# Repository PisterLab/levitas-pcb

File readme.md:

# LeviTAS PCB

This is a PCB test platform originally built for the LeviTAS project.

A Raspberry Pi Pico microcontroller controls four 0-240V high voltage outputs and can simultaneously read from four FDC2112 capacitance sensors. The architecture and code should be straightforward to re-engineered to add more channels.

# Programming / Firmware

This is how to program the microcontroller.

## Introduction

This project uses the Raspberry Pi RP2350 microcontroller, which is mounted to a Raspberry Pi Pico 2 dev board that we solder onto the main project PCB. The dev board is cheap and convenient because in addition to the RP2350 itself it includes flash memory, an oscillator, and power circuitry that we'd otherwise have to include anyway. The programming is the same either way.

The RP2350 is uniquely good for our use case because we need (a) four I2C buses running in parallel to read FDC2112 capacitance sensors, for which we use the PIO modules available only on the RP2040 and RP2350, and (b) we'd like floating-point math support built into the hardware, which the RP2350 has but the RP2040 does not. An FPGA might accomplish roughly the same tasks but is much more expensive and complicated to use.

Programming the RP2350 microcontroller is officially supported in C++ or MicroPython. We use C++ to more easily write programs that satisfy tight timing constraints (e.g., making a control loop as fast as possible). See the Documentation section below for links to the official documentation.

Note we're specifically using the 2.0.0 version of the SDK (because that's what we started with and haven't bothered to update it). Updating this requires updating the pico-sdk subfolder, every mention of the SDK version in other configuration files, and the version of the picotool utility used to upload the software. To minimize compilation issues, we also specifically chose to put the SDK files inside this git repo instead of requiring them to be downloaded to an external directory and linked.

## Installation and Running

Use the following steps to set up a software build environment for the Pico firmware on Linux or Windows, or follow the [official getting started guide](https://datasheets.raspberrypi.com/pico/getting-started-with-pico.pdf) for more generic instructions.

On Linux:
- Install gcc-arm-none-eabi compiler (arm-non-eabi-gcc on nixos)
- Install newlib
- Install cmake and gnumake
- Install picotool
- Install picotool udev rules
- In `firmware` folder, run `make build` to compile code and `make reload` to download and run (or `make` to do both).
- Use your favorite serial monitor to see data the Pico sends over USB.

On Windows:
- Install [Microsoft VS Code](https://code.visualstudio.com/) (This is preferable to VSCodium because the easiest way to read data from the Pico over USB is the Microsoft VS Code Serial Monitor extension, which doesn't work with VSCodium)
- Install the official [Raspberry Pi Pico Visual Studio Code extension](https://marketplace.visualstudio.com/items?itemName=raspberry-pi.raspberry-pi-pico)
- Open the `firmware` folder in VS Code. The Pi Pico extension should automatically detect this as a Pico project, and enable several commands under its quick access menu (click the extension icon on the Activity Bar, then under "Project" should be "Debug Project", "Compile Project", "Run Project (USB)", etc).
- Use the following commands:
  - "Compile Project" will compile (only) the software and put the compiled executables in a `build` subfolder, but note that "Configure CMake" must be run first.
  - "Configure CMake" will create a `build` subfolder and prepare the compilation based on configuration information in the `CMakeLists.txt` file. This is run automatically when the folder is opened in VS Code if recognized by the Pico extension. NOTE: THIS MUST BE MANUALLY RE-RUN EVERY TIME YOU CHANGE `CMakeLists.txt` FOR THE CHANGES TO BE APPLIED!
  - "Run Project (USB)" will load the program onto a Rasberry Pi Pico 2 board connected over USB (specifically, by running the `picotool` command line utility). If the Pico is in BOOTSEL mode (achieved by holding down the BOOTSEL button before plugging in USB) it will probably work immediately. If not, uploading can still work if USB communication was enabled on the already-running Pico program (which it is for this software, as per `CMakeLists.txt`), though you might need to press "Run Project (USB)" twice.
  - "Debug Project" and "Flash Project (SWD)" do not work without use of the Raspberry Pi Debug Probe (which we don't have).
- To see data the Pico is sending over USB, open the "SERIAL MONITOR" tab on the lower VS Code panel that also has "TERMINAL", "DEBUG CONSOLE", etc., set to 115200 baud and the correct COM port. Note this requires `pico_enable_stdio_usb(levitas 1)` to be set in `CMakeLists.txt` and `stdio_init_all();` to be called in `main.c` (which they are).

## Notable Firmware files

Inside the `firmware` folder:

- `CMakeLists.txt` configures compilation, and must be manually changed to include new source code files or other settings (e.g., importing a new sublibrary for the Pico SDK)
- `src/main.c` is the main source code file and holds the main LeviTAS control loop.
  - by default, this only prints capacitive sensor readings over USB; high voltage is set to zero
  - uncomment code in the main loop to enable high voltage output
- `src/pio_i2c.c`, `src/pio_i2c.h`, and `src/pio_i2c.pio` together form a library that can run I2C communication via the Pico PIOs. `src/main.c` uses this library to run four I2C ports in parallel (to connect to four FDC2112 chips).
- the following test code is unused but can be enabled by changing `CMakeLists.txt` to make them the main project file instead of `main.c`:
  - `src/test_fdc2112_i2c.c` tests only two of the four connected FDC2112 chips by using the two hardware built-in I2C modules (instead of PIO)
  - `src/test_fdc2112_pio_i2c.c` tests all four connected FDC2112 chips using the PIO library, and is almost identical to code in `src/main.c`.
  - `src/test_max5715_spi.c` tests the MAX5715 DAC and high voltage output, and is almost identical to code in `src/main.c`.
  - `src/test_mpu6050_i2c.c` displays data the MPU6050 accelerometer on the PCB motherboard using one of the hardware built-in I2C modules.

Other files:
- `Makefile` is used only for compiling on Linux, not for VS Code
- `.vscode` and `pico_sdk_import.cmake` are used only for VS Code with the official Pico VS Code extension, not on Linux
- the `build` subfolder is automatically generated by cmake when compiling and contains compiled executables in several formats, including UF2.

## Data Collection

The `data-collection/collect-data.py` and `data-collection/graph-data.py` Python programs in the `data-collection` subfolder of the main git repo can be used to automatically read the data the microcontroller sends over USB, then graph it. This provides much more useful data than manually looking at the printed output in a serial monitor.

## Some Useful Notes

There are several ways to upload code to a RP2040 or RP2350 chip:
1. Put into BOOTSEL mode (on Pi Pico dev board, hold down BOOTSEL buton when connecting power/USB), at which point the built-in ROM makes it act like a USB mass storage device. Upload file. (To verify file uploaded correctly, use picotool)
2. Put into BOOTSEL mode, use picotool to upload file
3. If USB communication enabled, can use picotool to force exit into BOOTSEL mode (use "picotool load -f" or "-F") then reboot (convenient!). There's no need to press the BOOTSEL button anymore. Note that sometimes this doesn't work on the first try, but repeating the process usually works.
4. Use SWD debugging interface.
Using the BOOTSEL mode (options 1,2) is necessary on a new chip, but afterward, as long as a program with USB communication enabled is running, option 3 is much more convenient. This is what we generally use.

Notes on the C/C++ SDK (from PDF manual):
- Consists of a large number of CMake libraries (in pico-sdk/src/rp2_common), which must be linked in the per-project CMakeLists.txt
  - The default library used in most examples is pico_stdlib, which includes several other libraries
  - the include files are typically in pico-sdk/src/rp2_common/(CMake library name)/include/(pico, hardware, gpio, etc)/(header.h)
- Apparently has some ability to build/debug running on the host operating system instead of the RP2040?
- Definitions for dev boards are in pico-sdk/src-boards/include/boards/
- The PDF manual has a bunch of examples
- Standard stdin/stdout can use (chapter 2.7):
  - UART (easy) (enabled by default) (disable by calling pico_enable_stdio_uart in CMakeLists.txt)
  - a USB CDC ACM virtual serial port (via TinyUSB) (enable by linking pico_stdio_usb or calling pico_enable_stdio_usb in CMakeLists.txt)
        (this is generally my preference?)
  - serial wire debug link (semihosting)
  - Segger RTT
- Can use bi_decl() in C code to store information in compiled binaries that picotool can access (e.g., comments, pin numbers)

## Documentation

There is a large amount of good official documentation at the following links. The most useful documentation is noted.

https://www.raspberrypi.com/documentation/microcontrollers/

RP2350 microcontroller:
- https://www.raspberrypi.com/products/rp2350/
- (good details on RP2350 hardware/capabilities) https://datasheets.raspberrypi.com/rp2350/rp2350-datasheet.pdf
- https://datasheets.raspberrypi.com/rp2350/hardware-design-with-rp2350.pdf
- https://datasheets.raspberrypi.com/rp2350/rp2350-product-brief.pdf

Pico and Pico 2 dev boards (which are almost identical):
- https://datasheets.raspberrypi.com/pico/pico-datasheet.pdf
- (good software getting-started guide) https://datasheets.raspberrypi.com/pico/getting-started-with-pico.pdf

Programming with C/C++:
- https://github.com/raspberrypi/pico-sdk
- (code examples) https://github.com/raspberrypi/pico-examples
- https://www.raspberrypi.com/documentation/microcontrollers/c_sdk.html
- https://www.raspberrypi.com/documentation/pico-sdk/index_doxygen.html
- (good software getting-started guide) https://datasheets.raspberrypi.com/pico/getting-started-with-pico.pdf
- (very thorough reference) https://datasheets.raspberrypi.com/pico/raspberry-pi-pico-c-sdk.pdf

Picotool:
- An official (and open source) CLI tool to work with compiled binaries and communicate with boards when in BOOTSEL mode (using the PICOBOOT interface; see RP2040 datasheet). Used to load and verify programs.
- https://github.com/raspberrypi/picotool

Raspberry Pi Debug Probe:
- Device to use UART or SWD debugging. Optional. We don't have one.
- https://www.raspberrypi.com/products/debug-probe/
- https://www.raspberrypi.com/documentation/microcontrollers/debug-probe.html

# More pictures

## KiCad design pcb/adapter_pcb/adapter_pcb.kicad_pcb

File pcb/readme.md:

# Bill of Materials

MOTHERBOARD

|--------------------+-----------+-----------------------------------------+----------+--------------------------|
| TOTAL QTY TO ORDER | PER BOARD | part                                    | COST PER | DigiKey part             |
|--------------------+-----------+-----------------------------------------+----------+--------------------------|
|                  5 |         1 | RP2350 Pico 2 board (SC1631)            | $5       | 2648-SC1631CT-ND         |
|--------------------+-----------+-----------------------------------------+----------+--------------------------|
|                    |         2 | 220ohm R thru-hole                      |          | S220QCT-ND               |
|                    |         1 | LED 5mm thru-hole white                 |          | BL-BZX3V4V-1-B02-ND      |
|                    |         1 | LED 5mm thru-hole red                   |          | 754-WP7113SURCK-ND       |
|--------------------+-----------+-----------------------------------------+----------+--------------------------|
|                    |         4 | 100nF 0603 SMD caps                     |          | 311-1523-1-ND            |
|                    |         3 | 4.7uF 0805 SMD caps                     |          | 1276-1244-1-ND           |
|--------------------+-----------+-----------------------------------------+----------+--------------------------|
|                  5 |         1 | MAX5715AAUD+T DAC                       | $14.6    | 175-MAX5715AAUD+TCT-ND   |
|--------------------+-----------+-----------------------------------------+----------+--------------------------|
|                  5 |         1 | HV264 opamp                             | $7.8     | 150-HV264TS-GCT-ND       |
|                    |         1 | 1N4004 diode thru-hole                  |          | 4878-1N4004CT-ND         |
|--------------------+-----------+-----------------------------------------+----------+--------------------------|
|                    |         4 | 5kohm, thru-hole, 400V                  |          | CF12JT4K70CT-ND          |
|                 12 |         4 | PTC fuse PTCCL05H100SBE                 | $0.99    | BC3368-ND                |
|--------------------+-----------+-----------------------------------------+----------+--------------------------|
|                  0 |         1 | Q025-5C power supply                    |          | -                        |
|                  5 |         1 | TVS diode P6KE6.8A-E3/54                | $0.32    | P6KE6.8A-E3/54GICT-ND    |
|                 10 |         1 | 1Mohm, thru-hole, 400V                  | $0.03    | RNV14FAL1M00             |
|                    |         1 | 10nF, thru-hole, 400V                   |          | 495-75587-1-ND           |
|--------------------+-----------+-----------------------------------------+----------+--------------------------|
|                  3 |         1 | Stemma MPU-6050 accelerometer breakout  | $12.95   | 1528-3886-ND             |
|--------------------+-----------+-----------------------------------------+----------+--------------------------|
|                  6 |         2 | ZIF socket                              | $24.49   | A305-ND                  |
|                    |        10 | jumpers                                 |          |                          |
|                    |         3 | 20x breakaway male header pins          |          | 2057-PH1-20-UA-ND        |
|                    |         3 | 20x female header pins                  |          | S7053-ND                 |
|--------------------+-----------+-----------------------------------------+----------+--------------------------|
|                    |         1 | solder paste?                           |          | 315-NC191AX35T5-ND       |
|                    |         1 | rubber feet?                            |          | 3M156065-ND              |
|--------------------+-----------+-----------------------------------------+----------+--------------------------|
|                    |         8 | 100nF 0603 SMD caps                     |          | 311-1523-1-ND            |
|                    |         8 | 4.7uF 0805 SMD caps                     |          | 1276-1244-1-ND           |
|--------------------+-----------+-----------------------------------------+----------+--------------------------|
|                 15 |         4 | cap sensor FDC2112QDNTRQ1               | $6.59    | 296-44560-1-ND           |
|                    |         8 | resistor SMD 4.7k 0603                  |          | 311-4.7KGRCT-ND          |
|                    |         8 | resistor SMD 470  0603                  |          | A129684CT-ND             |
|                    |         8 | resistor SMD 0  0603 (just in case)     |          | RMCF0603ZT0R00CT-ND      |
|                    |         4 | inductor SMD 18uH 0603 MLF1608C180KTA00 |          | 445-1028-1-ND            |
|                    |         4 | cap SMD 33pF 0603                       |          | 478-KGM15ACG1H330JTCT-ND |
|--------------------+-----------+-----------------------------------------+----------+--------------------------|

Generate PCB gerbers according to
https://www.pcbway.com/blog/help_center/Generate_Gerber_file_from_Kicad.html
- use copper, paste, silkscreen, mask, edge.cuts
- uncheck "use extended x2 format"
- drill file with "minimal header" and "suppress leading zeros"

When ordering:
- remove label option
- extra urgent

# Accelerometer

Attached for board leveling and reference data.

Using breakout board instead of individual chip because I don't trust my soldering for something that small.

Can use either Adafruit Stemma MPU-6050 breakout or Stemma ADXL345 breakout (same board size, slightly more expensive).

# Motherboard/daughterboard connection

We attach the sensor daughterboard with an IC ZIF socket (well, two sockets). We use this instead of standard 0.1" header pins and sockets because inserting or removing header pins takes significant force, which can significantly shake or warp the daughterboard and might break the fragile MEMS devices on top. Ultimately, of course, we want to build a levitation system capable of sustaining high external forces, but our initial prototypes may not immediately reach that goal. That said, the motherboard PCB has footprints such that it can be assembled with standard female header pins instead of ZIF sockets with no other change in functionality.

The specific ZIF sockets se use are 32-6554-11 "CONN IC DIP SOCKET ZIF 32POS GLD" or 32-6554-10 "CONN IC DIP SOCKET ZIF 32POS TIN" from Aries Electronics due to their relatively high availability and robust construction.

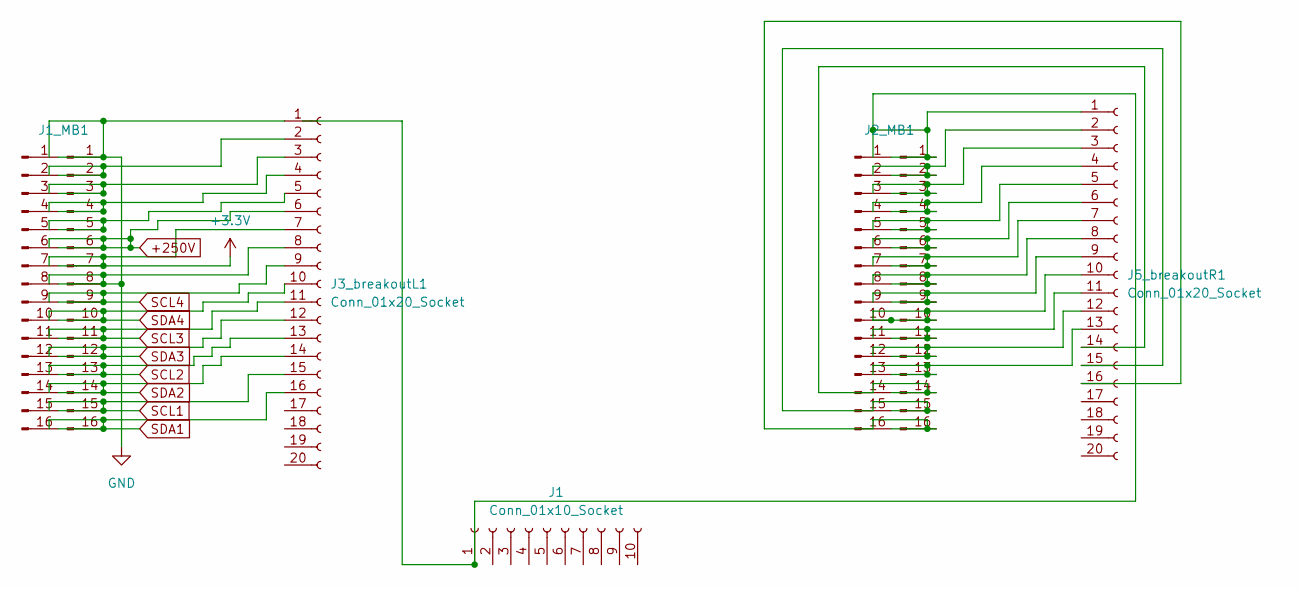
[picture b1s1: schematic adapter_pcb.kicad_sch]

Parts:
J1: Conn_01x10_Socket; wirebondarray-dteal
J1_MB1, J2_MB1, J3, J5: Conn_01x16_Pin; PinHeader_1x16_P2.54mm_Vertical
J3_breakoutL1, J5_breakoutR1: Conn_01x20_Socket; wirebondarray-1x20-emtan

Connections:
+3.3V: J1_MB1.7, J3.7, J3_breakoutL1.7
+250V: J1_MB1.6, J3.6, J3_breakoutL1.6
unnamed: J1_MB1.2, J3.2, J3_breakoutL1.2
unnamed: J1_MB1.3, J3.3, J3_breakoutL1.3
unnamed: J1_MB1.4, J3.4, J3_breakoutL1.4
unnamed: J1_MB1.5, J3.5, J3_breakoutL1.5
unnamed: J2_MB1.2, J5.2, J5_breakoutR1.2
unnamed: J2_MB1.3, J5.3, J5_breakoutR1.3
unnamed: J2_MB1.4, J5.4, J5_breakoutR1.4
unnamed: J2_MB1.5, J5.5, J5_breakoutR1.5
unnamed: J2_MB1.6, J5.6, J5_breakoutR1.6
unnamed: J2_MB1.7, J5.7, J5_breakoutR1.7
unnamed: J2_MB1.8, J5.8, J5_breakoutR1.8
unnamed: J2_MB1.9, J5.9, J5_breakoutR1.9
unnamed: J2_MB1.10, J5.10, J5_breakoutR1.10
unnamed: J2_MB1.11, J5.11, J5_breakoutR1.11
unnamed: J2_MB1.12, J5.12, J5_breakoutR1.12
unnamed: J2_MB1.13, J5.13, J5_breakoutR1.13
unnamed: J2_MB1.14, J5.14, J5_breakoutR1.14
unnamed: J2_MB1.15, J5.15, J5_breakoutR1.15
unnamed: J2_MB1.16, J5.16, J5_breakoutR1.16
SCL1: J1_MB1.15, J3.15, J3_breakoutL1.15
SCL2: J1_MB1.13, J3.13, J3_breakoutL1.13
SCL3: J1_MB1.11, J3.11, J3_breakoutL1.11
SCL4: J1_MB1.9, J3.9, J3_breakoutL1.9
SDA1: J1_MB1.16, J3.16, J3_breakoutL1.16
SDA2: J1_MB1.14, J3.14, J3_breakoutL1.14
SDA3: J1_MB1.12, J3.12, J3_breakoutL1.12
SDA4: J1_MB1.10, J3.10, J3_breakoutL1.10

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
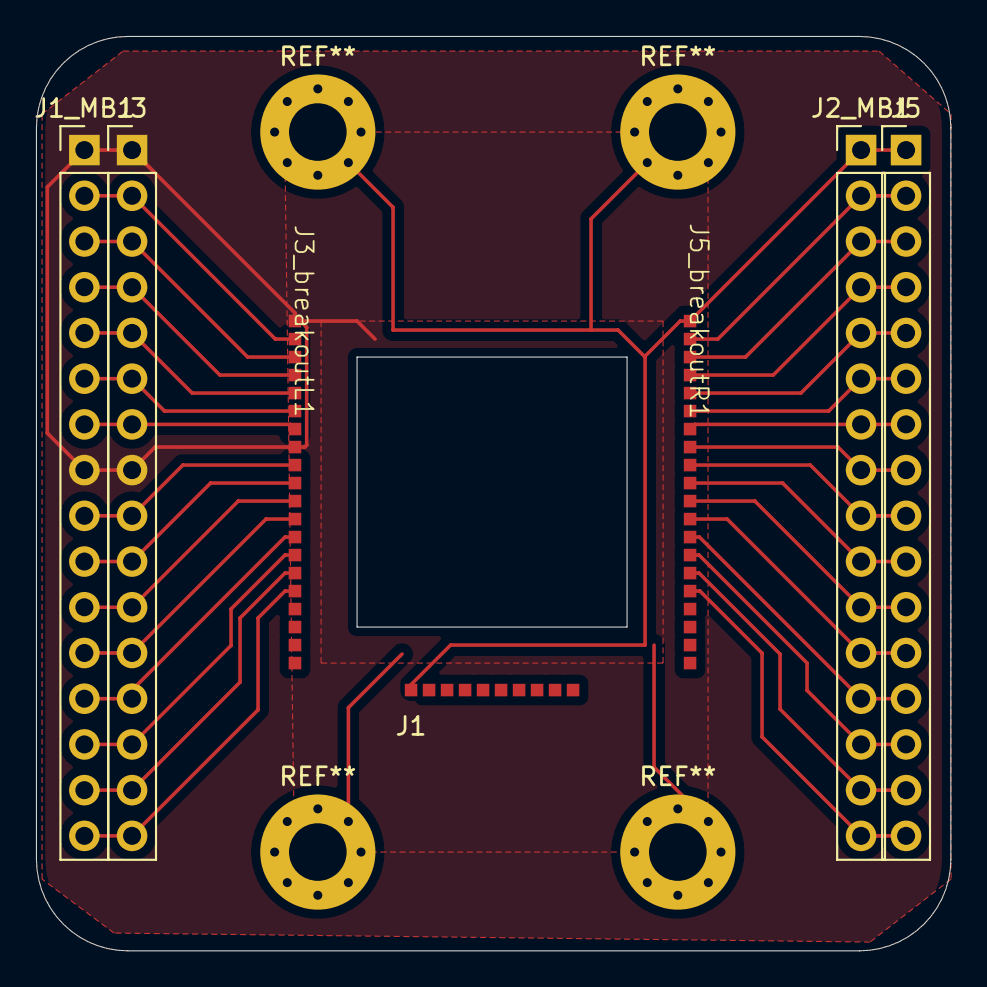
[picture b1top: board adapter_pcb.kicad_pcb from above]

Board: 2 copper layers, 50.8 x 50.8 mm, 7 parts (0 on the bottom side), 31 nets.

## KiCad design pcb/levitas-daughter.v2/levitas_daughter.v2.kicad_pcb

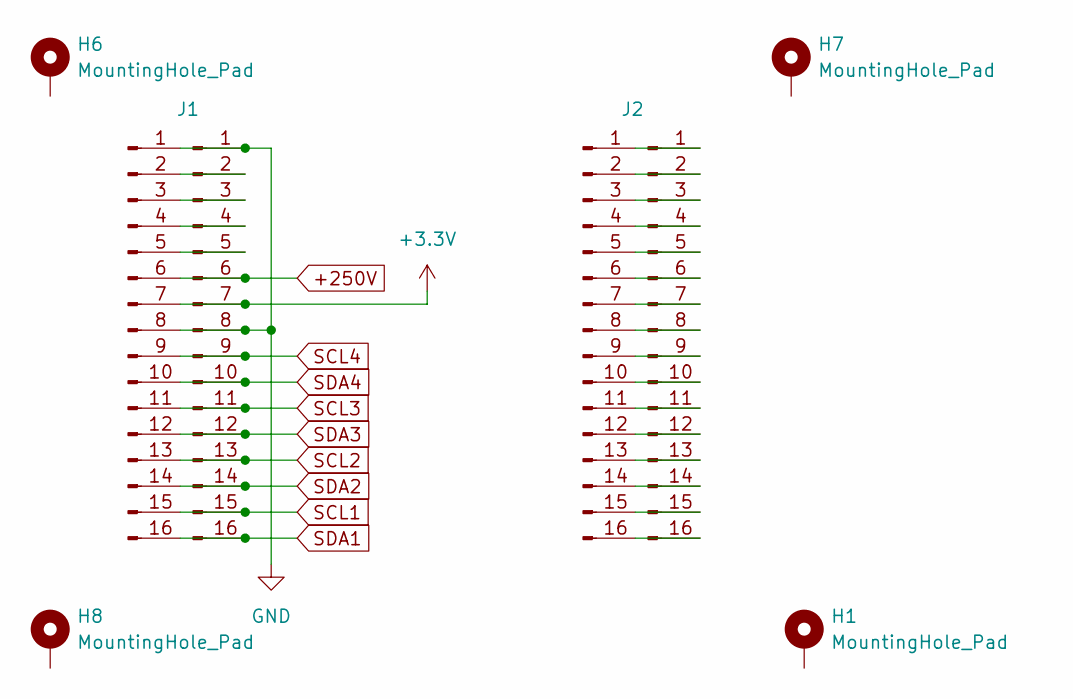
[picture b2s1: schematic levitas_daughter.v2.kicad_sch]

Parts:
H1, H6, H7, H8: MountingHole_Pad; MountingHole_3.2mm_M3_Pad_Via
J1, J2, J3, J4: Conn_01x16_Pin; PinHeader_1x16_P2.54mm_Vertical

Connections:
+3.3V: J1.7, J3.7
+250V: J1.6, J3.6
GND: J1.1, J1.8, J3.1, J3.8
unnamed: J1.2, J3.2
unnamed: J1.3, J3.3
unnamed: J1.4, J3.4
unnamed: J1.5, J3.5
unnamed: J2.1, J4.1
unnamed: J2.2, J4.2
unnamed: J2.3, J4.3
unnamed: J2.4, J4.4
unnamed: J2.5, J4.5
unnamed: J2.6, J4.6
unnamed: J2.7, J4.7
unnamed: J2.8, J4.8
unnamed: J2.9, J4.9
unnamed: J2.10, J4.10
unnamed: J2.11, J4.11
unnamed: J2.12, J4.12
unnamed: J2.13, J4.13
unnamed: J2.14, J4.14
unnamed: J2.15, J4.15
unnamed: J2.16, J4.16
SCL1: J1.15, J3.15
SCL2: J1.13, J3.13
SCL3: J1.11, J3.11
SCL4: J1.9, J3.9
SDA1: J1.16, J3.16
SDA2: J1.14, J3.14
SDA3: J1.12, J3.12
SDA4: J1.10, J3.10

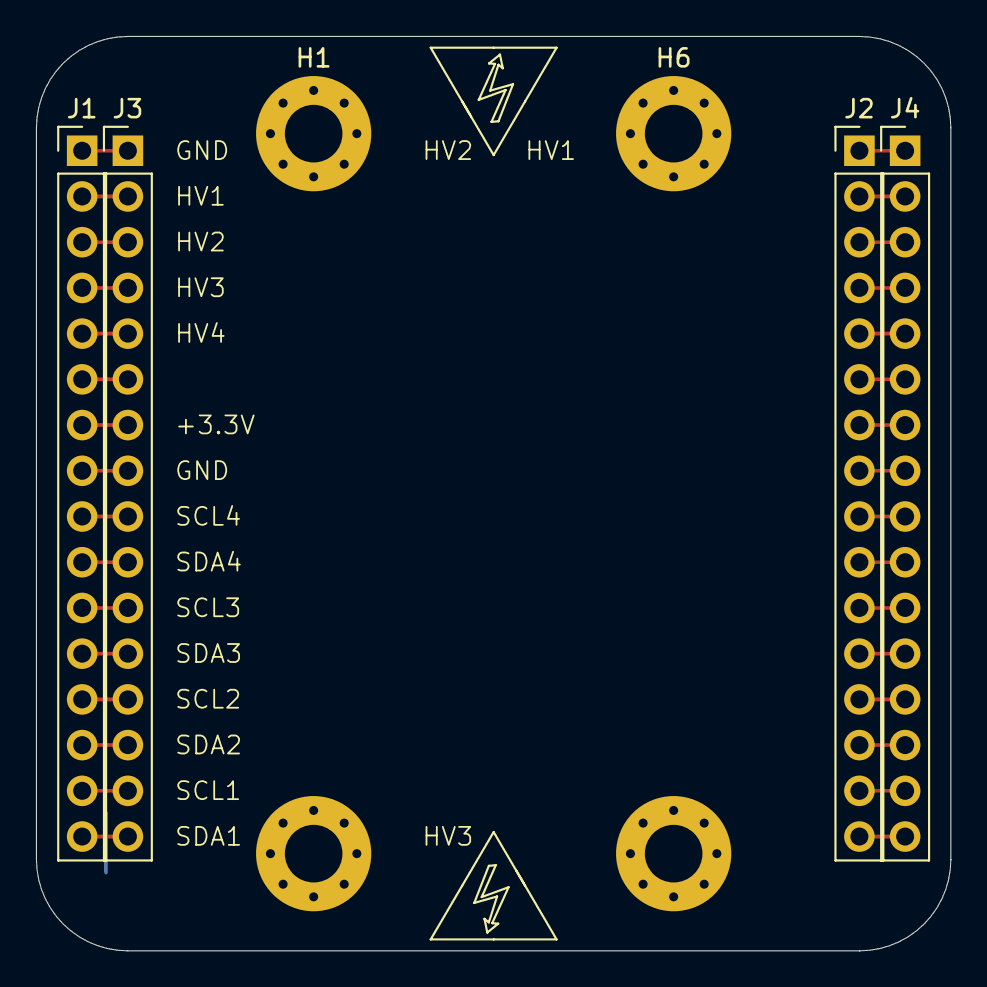
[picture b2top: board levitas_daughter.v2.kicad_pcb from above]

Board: 2 copper layers, 50.8 x 50.8 mm, 8 parts (0 on the bottom side), 31 nets.

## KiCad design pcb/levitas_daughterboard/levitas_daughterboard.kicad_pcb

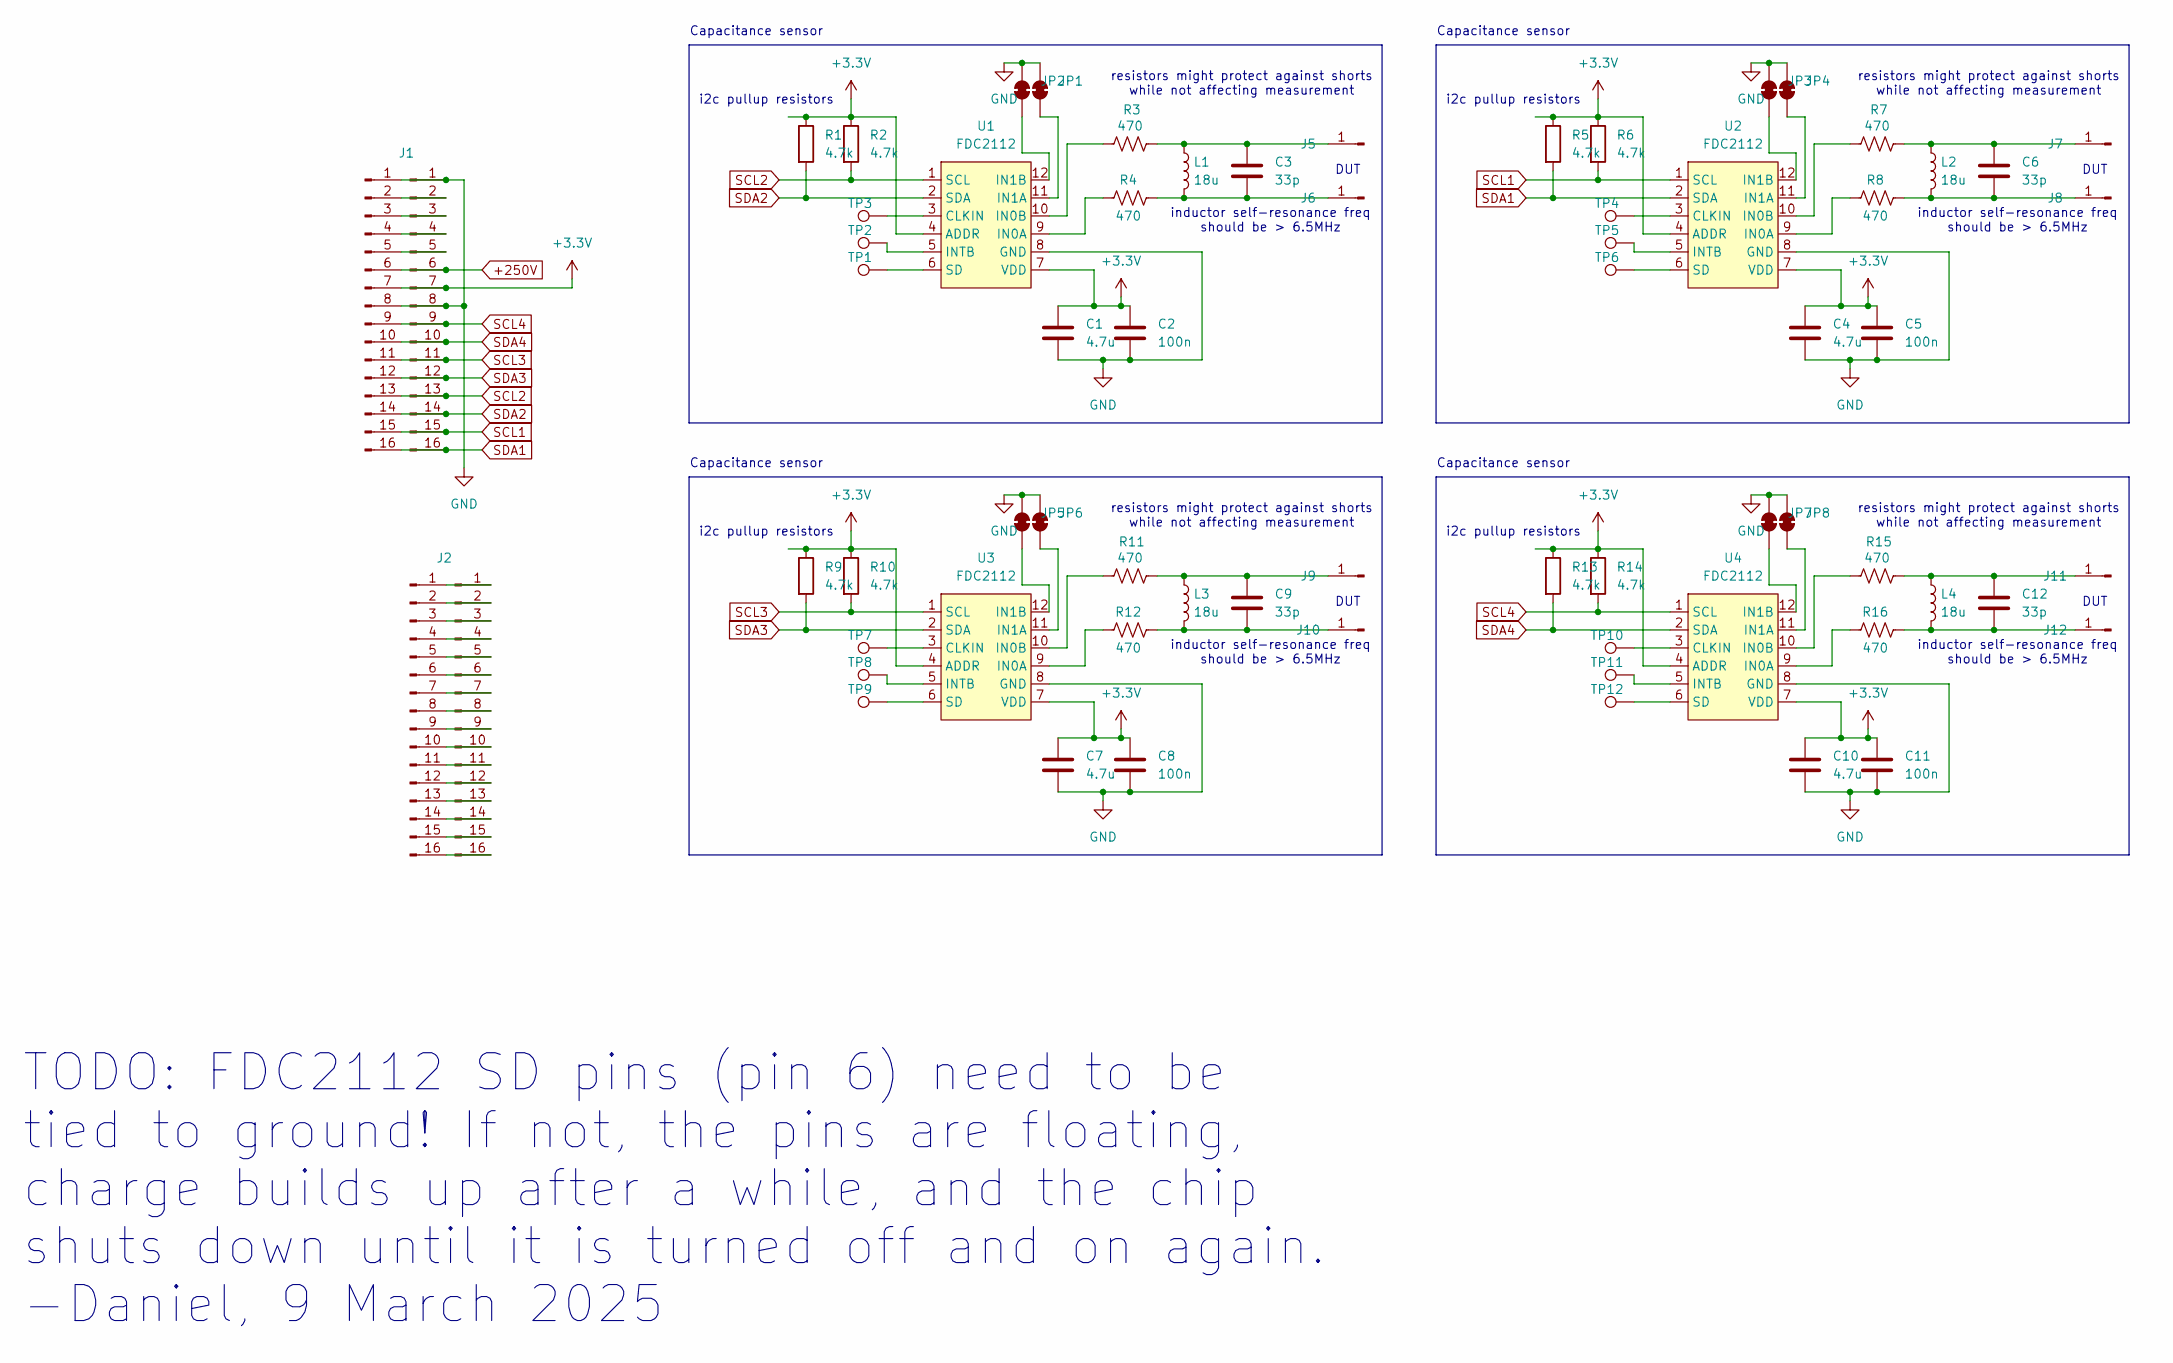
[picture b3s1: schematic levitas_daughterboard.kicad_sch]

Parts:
C1, C4, C7, C10: 4.7u; C_0805_2012Metric
C2, C5, C8, C11: 100n; C_0603_1608Metric
C3, C6, C9, C12: 33p; C_0504_1310Metric_Pad0.83x1.28mm_HandSolder
J1, J2, J3, J4: Conn_01x16_Pin; PinHeader_1x16_P2.54mm_Vertical
J5, J6, J7, J8, J9, J10, J11, J12: Conn_01x01_Pin; cap_sensor
JP1, JP2, JP3, JP4, JP5, JP6, JP7, JP8: SolderJumper_2_Bridged; SolderJumper-2_P1.3mm_Bridged_RoundedPad1.0x1.5mm
L1, L2, L3, L4: 18u; L_0603_1608Metric
R1, R2, R5, R6, R9, R10, R13, R14: 4.7k; R_0603_1608Metric
R3, R4, R7, R8, R11, R12, R15, R16: 470; R_0603_1608Metric
TP1, TP2, TP3, TP4, TP5, TP6, TP7, TP8, TP9, TP10, TP11, TP12: TestPoint; TestPoint_Pad_D1.0mm
U1, U2, U3, U4: FDC2112; WSON-12-1EP_4x4mm_P0.5mm_EP2.6x3mm

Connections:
+3.3V: C1.1, C2.1, C4.1, C5.1, C7.1, C8.1, C10.1, C11.1, J1.7, J3.7, R1.1, R2.1, R5.1, R6.1, R9.1, R10.1, R13.1, R14.1, U1.4 (ADDR), U1.7 (VDD), U2.4 (ADDR), U2.7 (VDD), U3.4 (ADDR), U3.7 (VDD), U4.4 (ADDR), U4.7 (VDD)
+250V: J1.6, J3.6
GND: C1.2, C2.2, C4.2, C5.2, C7.2, C8.2, C10.2, C11.2, J1.1, J1.8, J3.1, J3.8, JP1.2 (B), JP2.2 (B), JP3.2 (B), JP4.2 (B), JP5.2 (B), JP6.2 (B), JP7.2 (B), JP8.2 (B), U1.8 (GND), U2.8 (GND), U3.8 (GND), U4.8 (GND)
unnamed: J1.2, J3.2
unnamed: J1.3, J3.3
unnamed: J1.4, J3.4
unnamed: J1.5, J3.5
unnamed: J2.1, J4.1
unnamed: J2.2, J4.2
unnamed: J2.3, J4.3
unnamed: J2.4, J4.4
unnamed: J2.5, J4.5
unnamed: J2.6, J4.6
unnamed: J2.7, J4.7
unnamed: J2.8, J4.8
unnamed: J2.9, J4.9
unnamed: J2.10, J4.10
unnamed: J2.11, J4.11
unnamed: J2.12, J4.12
unnamed: J2.13, J4.13
unnamed: J2.14, J4.14
unnamed: J2.15, J4.15
unnamed: J2.16, J4.16
unnamed: C3.1, J5.1, L1.1, R3.1
unnamed: C3.2, J6.1, L1.2, R4.1
unnamed: C6.1, J7.1, L2.1, R7.1
unnamed: C6.2, J8.1, L2.2, R8.1
unnamed: C9.1, J9.1, L3.1, R11.1
unnamed: C9.2, J10.1, L3.2, R12.1
unnamed: C12.1, J11.1, L4.1, R15.1
unnamed: C12.2, J12.1, L4.2, R16.1
unnamed: JP1.1 (A), U1.11 (IN1A)
unnamed: JP2.1 (A), U1.12 (IN1B)
unnamed: JP3.1 (A), U2.12 (IN1B)
unnamed: JP4.1 (A), U2.11 (IN1A)
unnamed: JP5.1 (A), U3.12 (IN1B)
unnamed: JP6.1 (A), U3.11 (IN1A)
unnamed: JP7.1 (A), U4.12 (IN1B)
unnamed: JP8.1 (A), U4.11 (IN1A)
unnamed: TP3.1, U1.3 (CLKIN)
unnamed: R4.2, U1.9 (IN0A)
unnamed: R3.2, U1.10 (IN0B)
unnamed: TP2.1, U1.5 (INTB)
unnamed: TP1.1, U1.6 (SD)
unnamed: TP4.1, U2.3 (CLKIN)
unnamed: R8.2, U2.9 (IN0A)
unnamed: R7.2, U2.10 (IN0B)
unnamed: TP5.1, U2.5 (INTB)
unnamed: TP6.1, U2.6 (SD)
unnamed: TP7.1, U3.3 (CLKIN)
unnamed: R12.2, U3.9 (IN0A)
unnamed: R11.2, U3.10 (IN0B)
unnamed: TP8.1, U3.5 (INTB)
unnamed: TP9.1, U3.6 (SD)
unnamed: TP10.1, U4.3 (CLKIN)
unnamed: R16.2, U4.9 (IN0A)
unnamed: R15.2, U4.10 (IN0B)
unnamed: TP11.1, U4.5 (INTB)
unnamed: TP12.1, U4.6 (SD)
SCL1: J1.15, J3.15, R6.2, U2.1 (SCL)
SCL2: J1.13, J3.13, R2.2, U1.1 (SCL)
SCL3: J1.11, J3.11, R10.2, U3.1 (SCL)
SCL4: J1.9, J3.9, R14.2, U4.1 (SCL)
SDA1: J1.16, J3.16, R5.2, U2.2 (SDA)
SDA2: J1.14, J3.14, R1.2, U1.2 (SDA)
SDA3: J1.12, J3.12, R9.2, U3.2 (SDA)
SDA4: J1.10, J3.10, R13.2, U4.2 (SDA)

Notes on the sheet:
Capacitance sensor
inductor self-resonance freq should be > 6.5MHz
resistors might protect against shorts while not affecting measurement
i2c pullup resistors
DUT
TODO: FDC2112 SD pins (pin 6) need to be tied to ground! If not, the pins are floating, charge builds up after a while, and the chip shuts down until it is turned off and on again. -Daniel, 9 March 2025

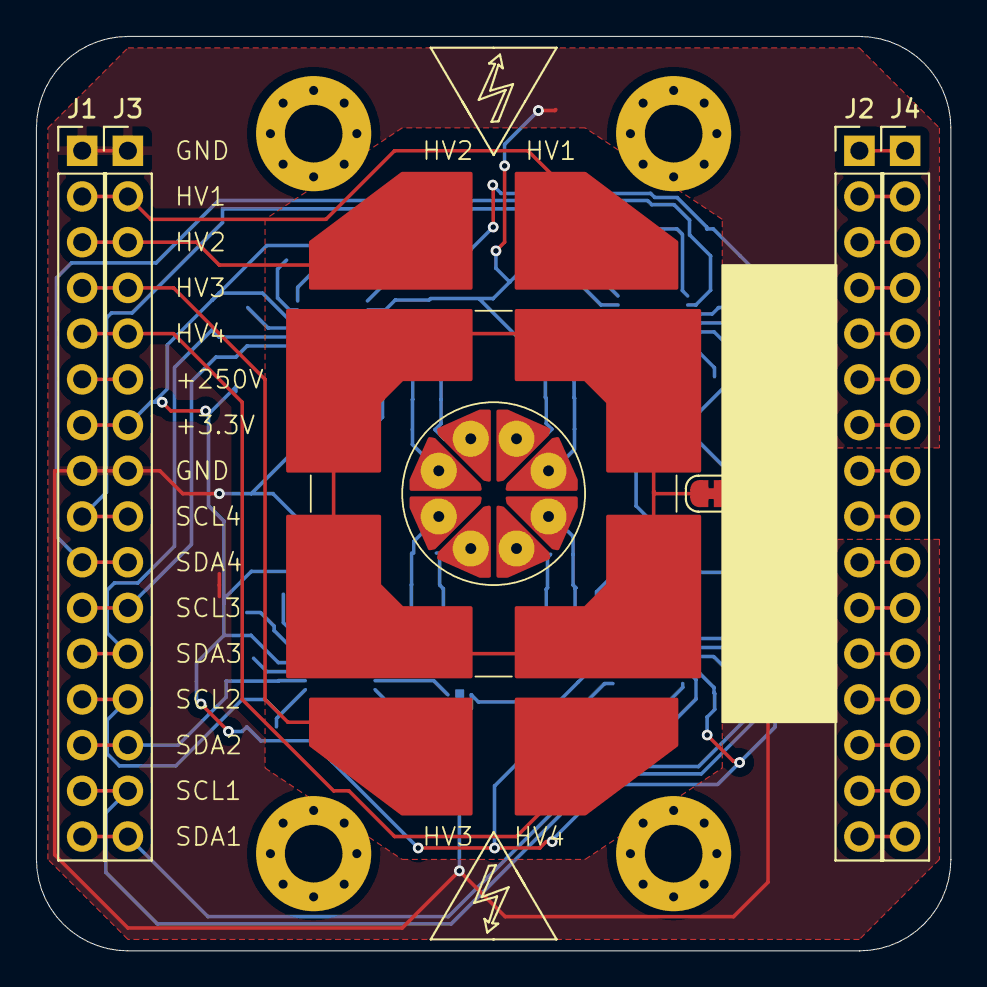
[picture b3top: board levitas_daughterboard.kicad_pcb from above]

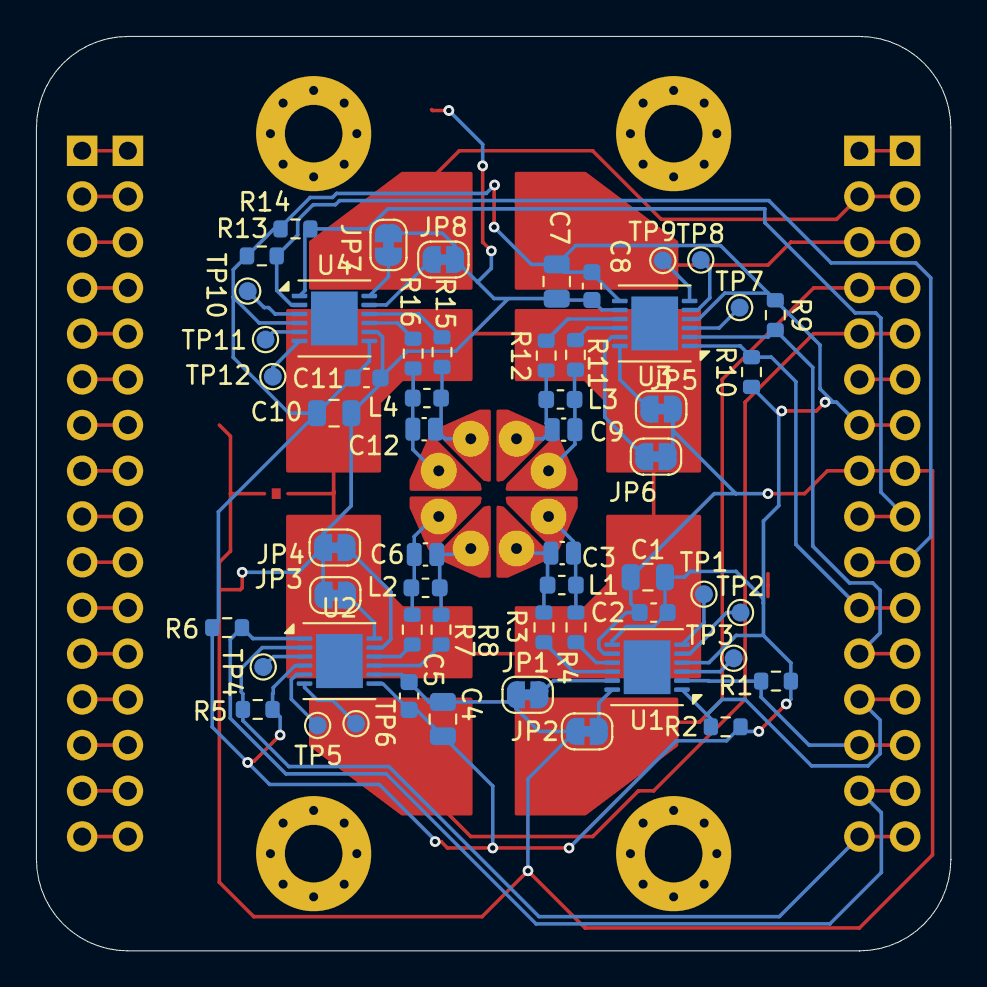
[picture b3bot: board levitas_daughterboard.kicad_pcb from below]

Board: 2 copper layers, 50.8 x 50.8 mm, 68 parts (62 on the bottom side), 67 nets.

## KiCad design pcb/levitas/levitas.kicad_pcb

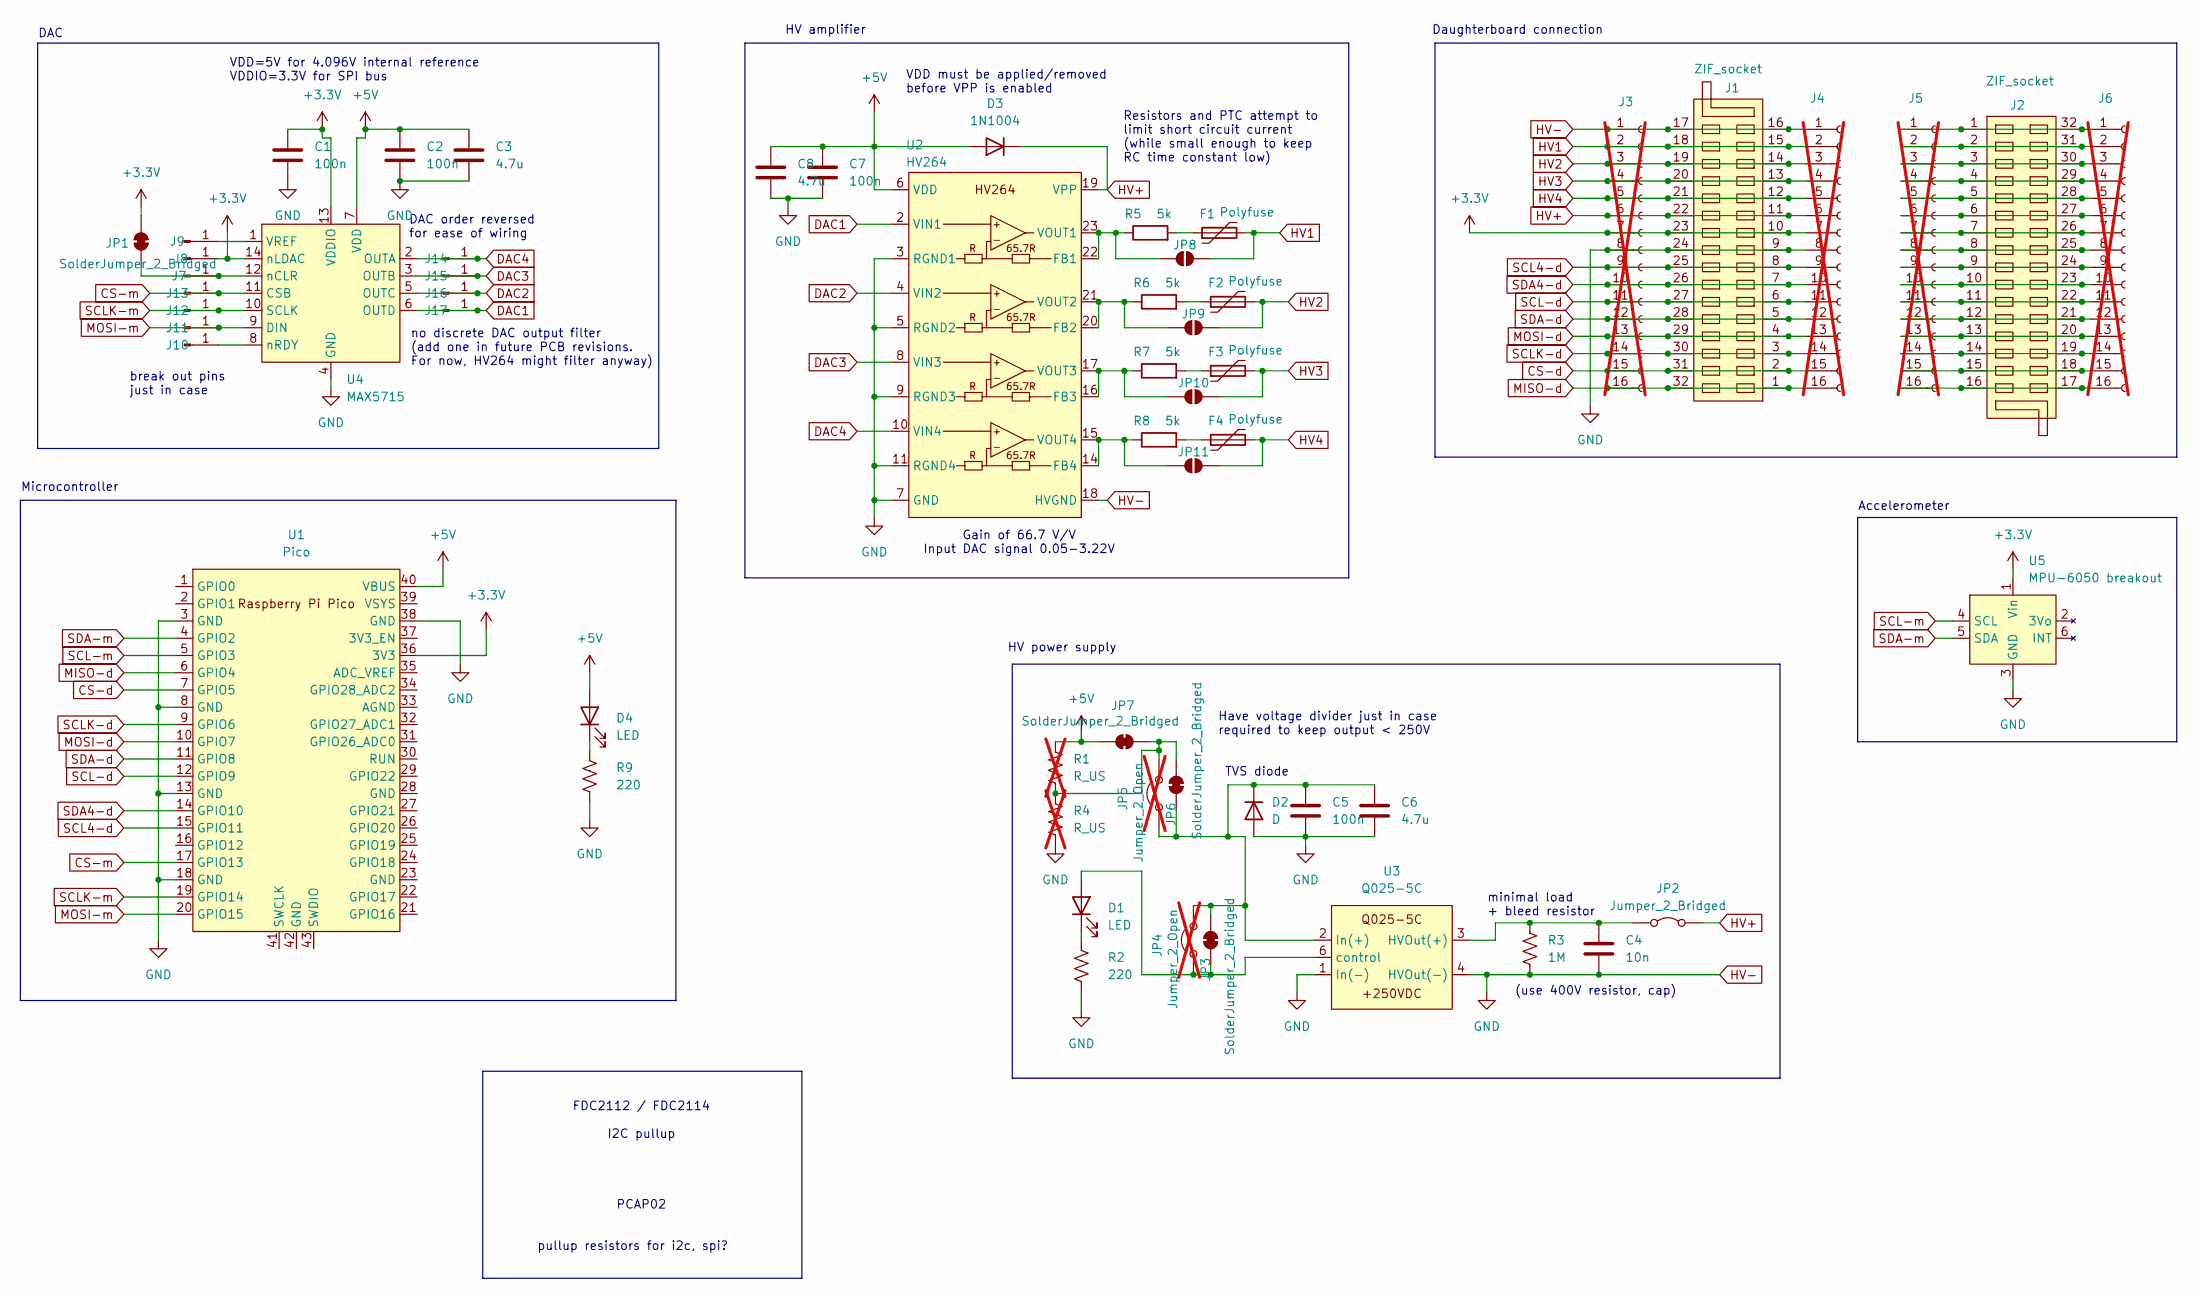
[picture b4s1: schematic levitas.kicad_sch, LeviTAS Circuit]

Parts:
C1, C2, C5, C7: 100n; C_0603_1608Metric
C3, C6, C8: 4.7u; C_0805_2012Metric
C4: 10n; C_Disc_D7.5mm_W2.5mm_P5.00mm
D1, D4: LED; LED_D5.0mm
D2: D; D_DO-41_SOD81_P10.16mm_Horizontal
D3: 1N1004; D_DO-41_SOD81_P10.16mm_Horizontal
F1, F2, F3, F4: Polyfuse; R_Axial_DIN0207_L6.3mm_D2.5mm_P7.62mm_Horizontal
J1, J2: ZIF_socket
J3, J4, J5, J6: Conn_01x16_Socket; PinSocket_1x16_P2.54mm_Vertical; not fitted
J7, J8, J9, J10, J11, J12, J13, J14, J15, J16, J17: Conn_01x01_Pin; TestPoint_Pad_D2.0mm
JP1, JP3, JP6, JP7: SolderJumper_2_Bridged; SolderJumper-2_P1.3mm_Bridged_RoundedPad1.0x1.5mm
JP2: Jumper_2_Bridged; PinHeader_1x02_P2.54mm_Vertical
JP4, JP5: Jumper_2_Open; PinHeader_1x02_P2.54mm_Vertical; not fitted
JP8, JP9, JP10, JP11: SolderJumper_2_Open; SolderJumper-2_P1.3mm_Open_RoundedPad1.0x1.5mm
R1, R4: R_US; R_Axial_DIN0207_L6.3mm_D2.5mm_P7.62mm_Horizontal; not fitted
R2, R9: 220; R_Axial_DIN0207_L6.3mm_D2.5mm_P7.62mm_Horizontal
R3: 1M; R_Axial_DIN0207_L6.3mm_D2.5mm_P7.62mm_Horizontal
R5, R6, R7, R8: 5k; R_Axial_DIN0207_L6.3mm_D2.5mm_P7.62mm_Horizontal
U1: Pico; RPi_Pico_SMD_TH
U2: HV264; TSSOP-24_4.4x7.8mm_P0.65mm
U3: Q025-5C
U4: MAX5715; TSSOP-14_4.4x5mm_P0.65mm
U5: MPU-6050 breakout; MPU-6050-breakout

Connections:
+3.3V: C1.1, J1.10, J1.23, J3.7, J4.7, J8.1, JP1.1 (A), U1.36 (3V3), U4.13 (VDDIO), U4.14 (nLDAC), U5.1 (Vin)
+5V: C2.1, C3.1, C7.1, C8.1, D3.2 (A), D4.2 (A), JP7.2 (B), R1.1, U1.40 (VBUS), U2.6 (VDD), U4.7 (VDD)
CS-d: J1.2, J1.31, J3.15, J4.15, U1.7 (GPIO5)
CS-m: J13.1, U1.17 (GPIO13), U4.11 (CSB)
DAC1: J17.1, U2.2 (VIN1), U4.6 (OUTD)
DAC2: J16.1, U2.4 (VIN2), U4.5 (OUTC)
DAC3: J15.1, U2.8 (VIN3), U4.3 (OUTB)
DAC4: J14.1, U2.10 (VIN4), U4.2 (OUTA)
HV1: F1.2, J1.15, J1.18, J3.2, J4.2, JP8.2 (B)
HV2: F2.2, J1.14, J1.19, J3.3, J4.3, JP9.2 (B)
HV3: F3.2, J1.13, J1.20, J3.4, J4.4, JP10.2 (B)
HV4: F4.2, J1.12, J1.21, J3.5, J4.5, JP11.2 (B)
HV+: D3.1 (K), J1.11, J1.22, J3.6, J4.6, JP2.2 (B), U2.19 (VPP)
HV-: C1.2, C2.2, C3.2, C4.2, C5.2, C6.2, C7.2, C8.2, D2.2 (A), J1.9, J1.16, J1.17, J1.24, J3.1, J3.8, J4.1, J4.8, R2.2, R3.2, R4.2, R9.2, U1.3 (GND), U1.8 (GND), U1.13 (GND), U1.18 (GND), U1.38 (GND), U2.3 (RGND1), U2.5 (RGND2), U2.7 (GND), U2.9 (RGND3), U2.11 (RGND4), U2.18 (HVGND), U3.1 (In(-)), U3.4 (HVOut(-)), U4.4 (GND), U5.3 (GND)
MISO-d: J1.1, J1.32, J3.16, J4.16, U1.6 (GPIO4)
MOSI-d: J1.4, J1.29, J3.13, J4.13, U1.10 (GPIO7)
MOSI-m: J11.1, U1.20 (GPIO15), U4.9 (DIN)
unnamed: D1.2 (A), JP3.1 (A), JP4.1 (A), U3.6 (control)
unnamed: D1.1 (K), R2.1
unnamed: C5.1, C6.1, D2.1 (K), JP3.2 (B), JP4.2 (B), JP5.1 (A), JP6.1 (A), U3.2 (In(+))
unnamed: D4.1 (K), R9.1
unnamed: F1.1, R5.2
unnamed: F2.1, R6.2
unnamed: F3.1, R7.2
unnamed: F4.1, R8.2
unnamed: J2.1, J2.32, J5.1, J6.1
unnamed: J2.2, J2.31, J5.2, J6.2
unnamed: J2.3, J2.30, J5.3, J6.3
unnamed: J2.4, J2.29, J5.4, J6.4
unnamed: J2.5, J2.28, J5.5, J6.5
unnamed: J2.6, J2.27, J5.6, J6.6
unnamed: J2.7, J2.26, J5.7, J6.7
unnamed: J2.8, J2.25, J5.8, J6.8
unnamed: J2.9, J2.24, J5.9, J6.9
unnamed: J2.10, J2.23, J5.10, J6.10
unnamed: J2.11, J2.22, J5.11, J6.11
unnamed: J2.12, J2.21, J5.12, J6.12
unnamed: J2.13, J2.20, J5.13, J6.13
unnamed: J2.14, J2.19, J5.14, J6.14
unnamed: J2.15, J2.18, J5.15, J6.15
unnamed: J2.16, J2.17, J5.16, J6.16
unnamed: J7.1, JP1.2 (B), U4.12 (nCLR)
unnamed: J9.1, U4.1 (VREF)
unnamed: J10.1, U4.8 (nRDY)
unnamed: C4.1, JP2.1 (A), R3.1, U3.3 (HVOut(+))
unnamed: JP5.2 (B), JP6.2 (B), JP7.1 (A), R1.2, R4.1
unnamed: JP8.1 (A), R5.1, U2.22 (FB1), U2.23 (VOUT1)
unnamed: JP9.1 (A), R6.1, U2.20 (FB2), U2.21 (VOUT2)
unnamed: JP10.1 (A), R7.1, U2.16 (FB3), U2.17 (VOUT3)
unnamed: JP11.1 (A), R8.1, U2.14 (FB4), U2.15 (VOUT4)
SCL4-d: J1.8, J1.25, J3.9, J4.9, U1.15 (GPIO11)
SCL-d: J1.6, J1.27, J3.11, J4.11, U1.12 (GPIO9)
SCL-m: U1.5 (GPIO3), U5.4 (SCL)
SCLK-d: J1.3, J1.30, J3.14, J4.14, U1.9 (GPIO6)
SCLK-m: J12.1, U1.19 (GPIO14), U4.10 (SCLK)
SDA4-d: J1.7, J1.26, J3.10, J4.10, U1.14 (GPIO10)
SDA-d: J1.5, J1.28, J3.12, J4.12, U1.11 (GPIO8)
SDA-m: U1.4 (GPIO2), U5.5 (SDA)

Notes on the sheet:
DAC
Resistors and PTC attempt to limit short circuit current (while small enough to keep RC time constant low)
HV power supply
Gain of 66.7 V/V Input DAC signal 0.05-3.22V
minimal load + bleed resistor
TVS diode
FDC2112 / FDC2114 I2C pullup
DAC order reversed for ease of wiring
PCAP02
VDD=5V for 4.096V internal reference VDDIO=3.3V for SPI bus
Microcontroller
Have voltage divider just in case required to keep output < 250V
VDD must be applied/removed before VPP is enabled
Accelerometer
Daughterboard connection
(use 400V resistor, cap)
break out pins just in case
HV amplifier
no discrete DAC output filter (add one in future PCB revisions. For now, HV264 might filter anyway)
pullup resistors for i2c, spi?
